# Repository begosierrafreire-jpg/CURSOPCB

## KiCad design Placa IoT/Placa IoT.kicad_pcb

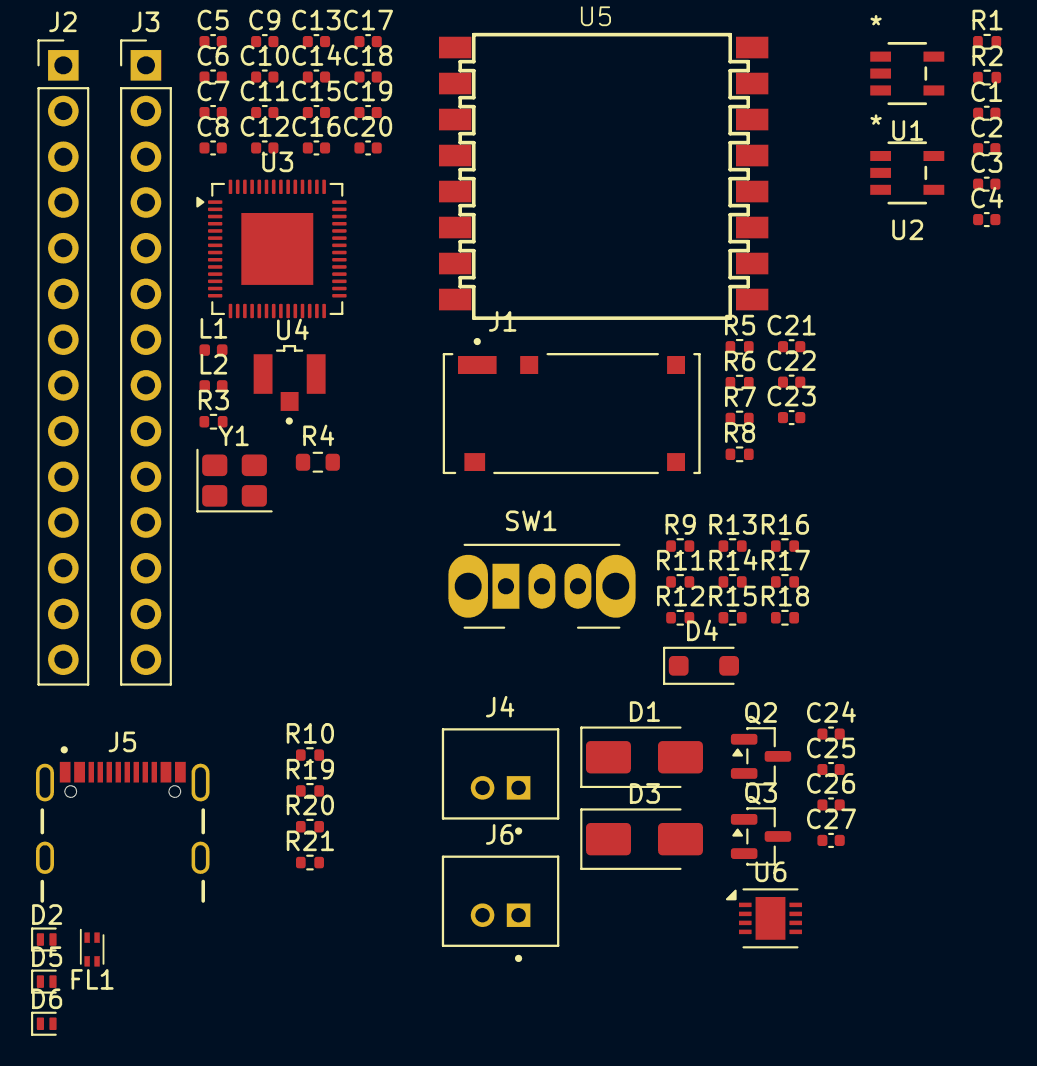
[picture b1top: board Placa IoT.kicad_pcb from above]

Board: 4 copper layers, 73 parts (0 on the bottom side), 55 nets, no tracks yet.

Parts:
C1, C2, C3, C4, C5, C6, C7, C12, C13, C14, C15, C16, C17, C18, C19: 100nF; C_0402_1005Metric
C8, C9, C20: 1nF; C_0402_1005Metric
C10, C11: 10nF; C_0402_1005Metric
C21, C22: NC; C_0402_1005Metric
C23, C24, C25, C26, C27: C; C_0402_1005Metric
D1, D3: SS34; D_SMA
D2, D5, D6: D_TVS; D_SOD-882
D4: SS34; D_SOD-123F
FL1: 0603USB-251; L_CommonModeChoke_Coilcraft_0603USB
J1: 20279-001E-03; ANTENNA_PIFA_3D_2.4GHZ
J2, J3: 22-28-4144; CONN_THT_MV_PH_P2.54MM_P14
J4, J6: B2B-PH-K-S(LF)(SN); CONN_THT_MV_JST_P2.00MM_P2
J5: USB4105-GF-A-120; CONN_SMT_RH_USBC_P0.50MM_P16
L1: 2nH; L_0402_1005Metric
L2: 22nH; L_0402_1005Metric
Q2, Q3: Q_PMOS; SOT-23
R1, R2: 10K; R_0402_1005Metric
R3: 499; R_0402_1005Metric
R4: 499; R_0603_1608Metric
R5, R6, R7, R8: 22; R_0402_1005Metric
R9, R10, R11, R12, R15, R16, R17, R18, R19, R20, R21: R; R_0402_1005Metric
R13, R14: 100K; R_0402_1005Metric
SW1: SW_SPDT; SW_Slide_SPDT_Angled_CK_OS102011MA1Q
U1, U2: RT9080-33GJ5; TSOT-23-5_RIT
U3: ESP32-S3; QFN-56-1EP_7x7mm_P0.4mm_EP4x4mm
U4: PRO-OB-536; IPEX_MHF_I
U5: T-SX1262; MODULE_T_SX1262
U6: CN3065; DFN-8-1EP_3x3mm_P0.5mm_EP1.66x2.38mm
Y1: 40 Mhz; Crystal_SMD_3225-4Pin_3.2x2.5mm

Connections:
+3.3VP: C4.1, J2.3
+3V3: C3.1, C5.1, C6.1, C7.1, C8.1, C9.1, C10.1, C20.1, L1.1, R3.1, U3.20 (VDD3P3_RTC), U3.46 (VDD3P3_CPU), U3.55 (VDDA), U3.56 (VDDA)
+5V: C1.1, C2.1, R1.1, R2.1, U1.1 (VIN), U2.1 (VIN)
/BATERIA/IO1: C27.1, R17.2, R18.1
/BATERIA/IO4: R13.2, R14.1
/BATERIA/SOLAR_IND: D4.1 (K), Q2.1 (G), R13.1
/BATERIA/VBUS: D1.2 (A), D3.2 (A), Q2.2 (S), Q3.1 (G), R9.1
/MCU_WIFI_BLU/IO8: J3.9, U3.13 (GPIO8)
/MCU_WIFI_BLU/IO12: J3.10, U3.17 (GPIO12)
/MCU_WIFI_BLU/IO15: J3.12, U3.21 (XTAL_32K_P)
/MCU_WIFI_BLU/IO16: J3.13, U3.22 (XTAL_32K_N)
/MCU_WIFI_BLU/IO33: J3.6, U3.38 (GPIO33)
/MCU_WIFI_BLU/IO34: J3.5, U3.39 (GPIO34)
/MCU_WIFI_BLU/IO35: J3.4, U3.40 (GPIO35)
/MCU_WIFI_BLU/IO36: J3.2, U3.41 (GPIO36)
/MCU_WIFI_BLU/IO37: J3.1, U3.42 (GPIO37)
/MCU_WIFI_BLU/IO38: J2.13, U3.43 (GPIO38)
/MCU_WIFI_BLU/IO39/MTCK: J2.10, U3.44 (MTCK)
/MCU_WIFI_BLU/IO40/MTDO: J2.9, U3.45 (MTDO)
/MCU_WIFI_BLU/IO41/MTDI: J2.8, U3.47 (MTDI)
/MCU_WIFI_BLU/IO45: J2.7, R3.2, U3.51 (GPIO45)
/MCU_WIFI_BLU/IO46: J2.6, U3.52 (GPIO46)
/MCU_WIFI_BLU/IO47: J3.7, U3.37 (SPICLK_P)
/MCU_WIFI_BLU/IO48: J3.8, U3.36 (SPICLK_N)
/MCU_WIFI_BLU/RST/EN: J3.11, U3.4 (CHIP_PU)
/MCU_WIFI_BLU/UOTXD: J2.12, R4.1, U3.50 (U0RXD)
/USB/D+: FL1.1, FL1.2, R10.1
/USB/D-: FL1.3, FL1.4, R19.1
GND: C1.2, C2.2, C3.2, C4.2, C5.2, C6.2, C7.2, C8.2, C11.2, C12.2, C13.2, C14.2, C15.2, C16.2, C17.2, C20.2, C21.2, C22.2, C24.2, C27.2, D2.1 (A1), D4.2 (A), D5.1 (A1), D6.1 (A1), J1.2 (Ext), J2.2, J2.4, J4.1 (Pin_1_1), J5.A1_B12 (GND), J5.B1_A12 (GND), J5.SH (SHIELD), J6.2, R9.2, R12.2, R14.2, R16.2, R18.2, R20.2, R21.2, U1.2 (GND), U2.2 (GND), U3.57 (GND), U4.1 (GND), U5.1 (GND), U5.8 (GND), U5.11 (NC), U5.15 (GND), U6.3 (GND), U6.9 (GND)
unnamed: C11.1, L1.2, U3.2 (VDD3P3), U3.3 (VDD3P3)
unnamed: C12.1, L2.1, Y1.1
unnamed: C15.1, C16.1, C19.1
unnamed: C22.1, C23.1
unnamed: D1.1 (K), Q3.2 (S), SW1.2 (B)
unnamed: D2.2 (A2), J5.A7 (D-), R19.2
unnamed: C24.1, C25.1, D3.1 (K), R11.1, R15.1, U6.4 (VIN)
unnamed: D5.2 (A2), J5.A6 (D+), R10.2
unnamed: D6.2 (A2), J5.A4_B9 (VBUS), J5.B4_A9 (VBUS)
unnamed: C21.1, C23.2, J1.1 (In)
unnamed: J5.A5 (CC1), R20.1
unnamed: J5.B5 (CC2), R21.1
unnamed: R6.1, U5.13 (NC)
unnamed: R1.2, U1.3 (EN)
unnamed: R2.2, U2.3 (EN)
unnamed: C14.1, C18.1, U3.1 (LNA_IN)
unnamed: C13.1, U3.53 (XTAL_N), Y1.3
unnamed: L2.2, U3.54 (XTAL_P)
unnamed: C17.1, C19.2, U4.2 (FEED)
unnamed: R8.1, U5.9 (BUSY)
unnamed: R7.1, U5.10 (DIO1)
unnamed: R5.1, U5.14 (DIO3)
unnamed: R12.1, U6.2 (ISET)
unnamed: R16.1, U6.1 (TEMP)
unnamed: Y1.2 (G), Y1.4 (G)
VBAT: C26.1, J2.14, J3.3, J3.14, J6.1, Q2.3 (D), Q3.3 (D), R17.1, U3.5 (GPIO0), U6.5 (BAT), U6.8 (FB)

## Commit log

2026-05-18 iniciar commit
2026-05-18 develop 1
2026-05-18 Projet create
2026-05-19 Añadir huella
2026-05-19 Añadir esquematico
2026-05-19 Alimentacion creada
2026-05-19 microcontorlador en proceso
2026-05-19 microcontrolador en procso 2
2026-05-19 microcontorlador en proceso 4
2026-05-20 microcontrolador en proceso 20052026
2026-05-20 microcortrolador en proceso 20052026
2026-05-20 Micrcontrolador en proceso 20252026
2026-05-20 SQUEMATIC FINISH
2026-05-20 ESQUEMA FINALIZADO
2026-05-20 ESQUEMA FIN
2026-05-21 ESQUEMA FIN 21052026
